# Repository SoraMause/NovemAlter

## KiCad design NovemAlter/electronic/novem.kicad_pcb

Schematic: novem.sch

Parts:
BZ1: Bz; CSS-0575A-SMT
C1: 470u; CP_Elec_8x10.5
C2, C11, C17: 10u; C_0603_HandSoldering_silk
C3: 22u; C_0603_HandSoldering_silk
C4, C10, C12, C13, C14, C16, C18, C20, C21, C23, C24: 0.1u; C_0603_HandSoldering_silk
C5, C6, C26: 10u; C_0805_HandSoldering_silk
C7, C30: 47u; C_1206_HandSoldering
C8, C28: 0.33u; C_0603_HandSoldering_silk
C9: 0.01u; C_0603_HandSoldering_silk
C15: 1u; C_0603_HandSoldering_silk
C19: 4.7u; C_0603_HandSoldering_silk
C22, C25, C27, C29: 2.2u; C_0603_HandSoldering_silk
CN1: CONNECT; Pin_Header_Straight_1x02_Pitch2.54mm
D1, D2, D4, D5: LED_ALT; IRED_D5.0mm_angled
D3, D7, D8: LED; LED_0603_HandSoldering_silk
D6: D; D_0603
D9: LATBT66B
J1: Conn_01x02_Female; Pin_Header_Straight_2x01_Pitch2.54mm
Q1: IRLML6402; SOT-23_Handsoldering
Q2, Q3, Q8, Q9: 2N7002; SOT-23_Handsoldering
Q4, Q5, Q6, Q7: Q_Photo_NPN; ST-1KL3A
R1, R6: 330; R_0603_HandSoldering_silk
R2, R3, R7, R14, R17, R23, R25, R26: 10k; R_0603_HandSoldering_silk
R4, R8: R; R_0805_HandSoldering_silk
R5, R9: 2.2k; R_0603_HandSoldering_silk
R10, R11, R12, R15, R16, R18, R19, R20, R21, R22: 1k; R_0603_HandSoldering_silk
R13: 510; R_0603_HandSoldering_silk
R24: 56k; R_0603_HandSoldering_silk
SW1: SW_SPST; PCM12SMTR
SW2, SW4: SW_Push; SKRPACE010
SW3: RESET; SKRPACE010
U1, U2: 1717_ie2_1024; Pin_Header_Straight_2x03_Pitch2.54mm
U3: AZ1117-5.0; SOT-223
U4: NJM2884-3.3; SOT-89-5_Housing_Handsoldering
U5: MPU-6500; QFN-24_3x3mm_Pitch0.4mm_silk
U6, U10: TB6614FNG; SSOP-16_4.4x5.2mm_Pitch0.65mm
U7: CSTCE12M0G52A; CSTCE12M0G52A-R0_HandSolding
U8: conn_02*03; SBH51LPSED03STBK
U9: STM32F405RGT; LQFP-64_10x10mm_Pitch0.5mm
U11: NJM2884-3.3; SOT-89-5_Housing

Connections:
+3V3: C26.1, C29.1, D4.2, D5.2, U11.4
GND: C1.2, C2.2, C3.2, C4.1, C5.2, C6.2, C7.2, C8.2, C9.2, C10.2, C11.1, C12.1, C13.2, C14.2, C15.2, C16.2, C17.1, C18.1, C19.2, C20.2, C21.2, C22.2, C23.2, C24.1, C25.1, C26.2, C27.1, C28.2, C29.2, C30.2, CN1.2, Q2.2 (S), Q3.2 (S), Q8.2 (S), Q9.2 (S), R3.2, R5.2, R7.2, R10.2, R11.2, R12.2, R14.1, R15.2, R16.2, R23.2, R24.2, R25.2, SW1.2, SW2.2, SW3.1, SW4.2, U1.3, U2.3, U3.1 (GND), U4.2, U5.11, U5.18, U5.20, U6.1, U6.5, U6.12, U7.2, U8.4, U9.12, U9.18, U9.63, U10.1, U10.5, U10.12, U11.2
IN1_L: U6.2, U9.36
IN1_R: U9.40, U10.2
IN2_L: U6.3, U9.35
IN2_R: U9.39, U10.3
MOTOR_L1: U1.1, U6.6, U6.7
MOTOR_L2: U1.2, U6.10, U6.11
MOTOR_R1: U2.1, U10.6, U10.7
MOTOR_R2: U2.2, U10.10, U10.11
unnamed: BZ1.2, D6.2, Q8.3 (D)
unnamed: C13.1, U5.10
unnamed: C14.1, SW3.2, U9.7
unnamed: C22.1, U9.31
unnamed: C25.2, U9.47
unnamed: D1.1, R8.1
unnamed: D1.2, D4.1
unnamed: D2.1, R4.1
unnamed: D2.2, D5.1
unnamed: D3.1, R5.1
unnamed: D7.1, R20.2
unnamed: D8.1, R21.2
unnamed: D9.1, R18.1
unnamed: D9.3, R22.1
unnamed: D9.4, R19.1
unnamed: J1.2, Q9.3 (D)
unnamed: Q1.1 (G), R2.1, SW1.1
unnamed: Q2.1 (G), R1.1, R3.1
unnamed: Q2.3 (D), R4.2
unnamed: Q3.1 (G), R6.1, R7.1
unnamed: Q3.3 (D), R8.2
unnamed: Q8.1 (G), R13.1, R14.2
unnamed: R24.1, U9.28
unnamed: U7.1, U9.5
unnamed: U7.3, U9.6
PWM_L: U6.14, U9.22
PWM_R: U9.23, U10.14
SCL: U5.23, U9.51
SD0: U5.9, U9.52
SDI: U5.24, U9.53
VBAT: C1.1, C2.1, C11.2, C17.2, D3.2, Q1.3 (D), R9.1, U3.3 (VI), U6.8, U6.9, U10.8, U10.9
VCC: C3.1, C5.1, C6.1, C8.1, C28.1, U1.4, U2.4, U3.2 (VO), U3.4, U4.1, U4.5, U11.1, U11.5
VDD: BZ1.1, C7.1, C9.1, C10.1, C12.2, C15.1, C16.1, C18.2, C19.1, C20.1, C21.1, C23.1, C24.2, C27.2, C30.1, D6.1, D7.2, D8.2, D9.2, Q4.1, Q5.1, Q6.1, Q7.1, R17.2, R26.2, U4.4, U5.8, U5.13, U6.15, U6.16, U8.1, U9.1, U9.13, U9.19, U9.32, U9.48, U9.64, U10.15, U10.16
batt_analog: C4.2, R9.2, R10.1, U9.25
boot: R23.1, U8.6, U9.60
buzzer_pwm: R13.2, U9.21
enc_LA: U1.5, U9.38
enc_LB: U1.6, U9.37
enc_RA: U2.5, U9.42
enc_RB: U2.6, U9.41
fledblue: R22.2, U9.3
fledgreen: R19.2, U9.62
fledred: R18.2, U9.61
fun: Q9.1 (G), R25.1, U9.55
fun_power: CN1.1, J1.1, Q1.2 (S), R2.2
gyro_cs: U5.22, U9.59
led1: R20.1, U9.20
led2: R21.1, U9.56
push1: R17.1, SW2.1, U9.24
push2: R26.1, SW4.1, U9.27
sensor0: Q4.2, R11.1, U9.8
sensor1: Q6.2, R15.1, U9.9
sensor2: Q5.2, R12.1, U9.16
sensor3: Q7.2, R16.1, U9.17
sensor_paluse_front: R1.2, U9.15
sensor_paluse_side: R6.2, U9.14
usart3_rx: U8.2, U9.30
usart3_tx: U8.3, U9.29

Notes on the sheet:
Use VCC Power
MOTOR,ENCODER
IRLED SFH4550
USE VDD LINE
BUZZER
LED,PUSHSW
WALL SENSOR ST-1KL3A
MCU
POWER
GYRO MPU-6500
MOTOR DRIVER

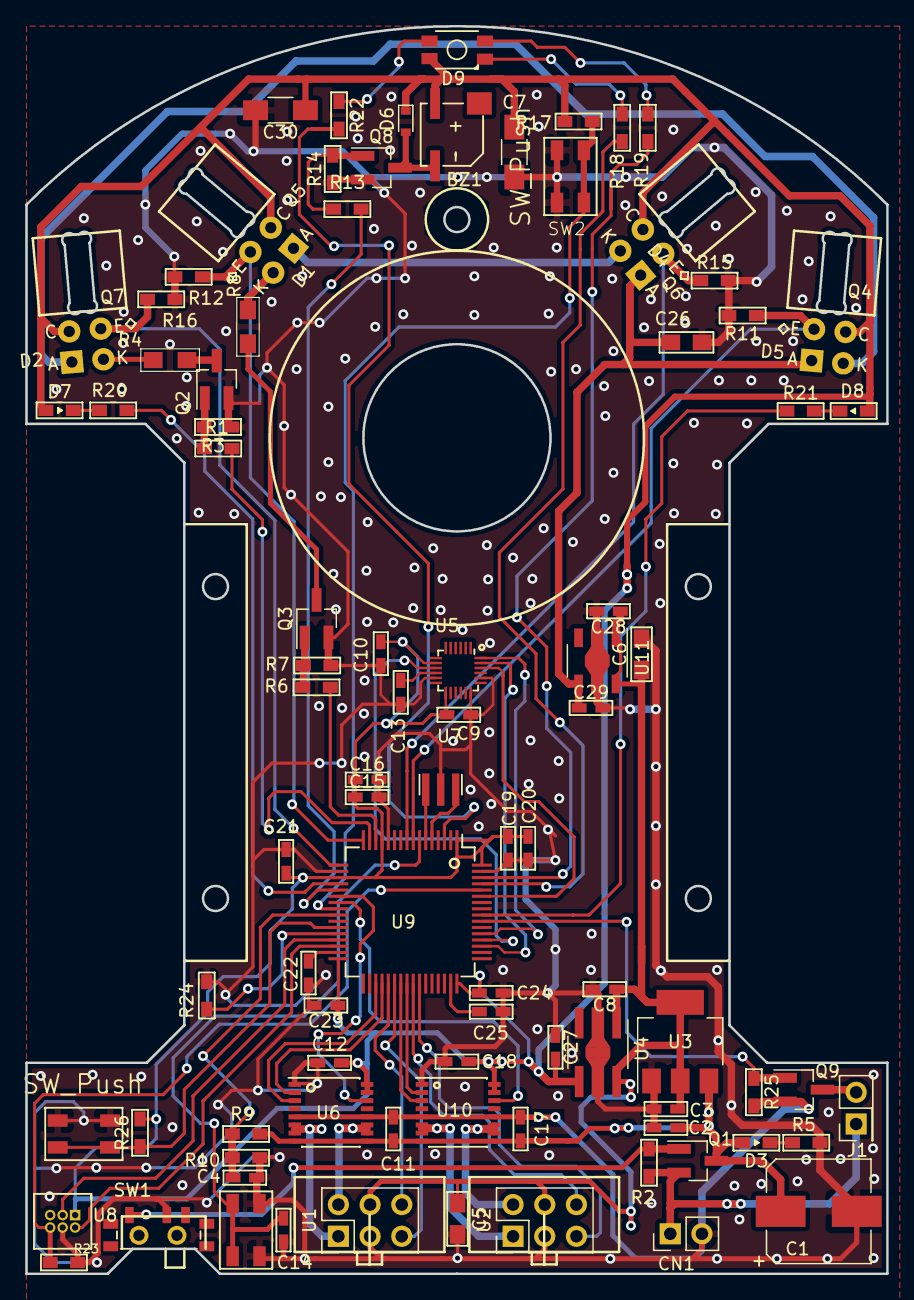
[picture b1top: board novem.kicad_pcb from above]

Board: 2 copper layers, 69.0 x 100.0 mm, 92 parts (0 on the bottom side), 68 nets.

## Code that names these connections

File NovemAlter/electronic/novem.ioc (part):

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Mcu.Name=STM32F405RGTx
Mcu.Package=LQFP64
Mcu.UserName=STM32F405RGTx
PA0-WKUP.GPIOParameters=GPIO_Label
PA0-WKUP.GPIO_Label=sensor_paluseSide
PA0-WKUP.Signal=GPIO_Output
PA1.GPIOParameters=GPIO_Label
PA1.GPIO_Label=sensor_paluseFront
PA1.Signal=GPIO_Output
PA2.Signal=ADCx_IN2
PA3.Signal=ADCx_IN3
PA4.GPIOParameters=GPIO_Label
PA4.GPIO_Label=led1
PA4.Signal=GPIO_Output
PA5.Signal=S_TIM2_CH1_ETR
PA6.Signal=S_TIM3_CH1
PA7.Signal=S_TIM3_CH2
PA8.Signal=S_TIM1_CH1
PA9.Signal=S_TIM1_CH2
PB1.GPIOParameters=GPIO_Label
PB1.GPIO_Label=push_sw2
PB1.Signal=GPIO_Input
PB10.Mode=Asynchronous
PB10.Signal=USART3_TX
PB11.Mode=Asynchronous
PB11.Signal=USART3_RX
PB14.GPIOParameters=GPIO_Label
PB14.GPIO_Label=IN2_L
PB14.Signal=GPIO_Output
PB15.GPIOParameters=GPIO_Label
PB15.GPIO_Label=IN1_L
PB15.Signal=GPIO_Output
PB3.Signal=S_TIM2_CH2
PB4.GPIOParameters=GPIO_Label
PB4.GPIO_Label=led2
PB4.Signal=GPIO_Output
PB7.GPIOParameters=GPIO_Label
PB7.GPIO_Label=gyro_cs
PB7.Signal=GPIO_Output
PB8.GPIOParameters=GPIO_Label
PB8.GPIO_Label=fledred
PB8.Signal=GPIO_Output
PB9.GPIOParameters=GPIO_Label
PB9.GPIO_Label=fledgreen
PB9.Signal=GPIO_Output
PC0.Signal=ADCx_IN10
PC1.Signal=ADCx_IN11
PC10.Mode=Full_Duplex_Master
PC10.Signal=SPI3_SCK
PC11.Mode=Full_Duplex_Master
PC11.Signal=SPI3_MISO
PC12.Mode=Full_Duplex_Master
PC12.Signal=SPI3_MOSI
PC14-OSC32_IN.GPIOParameters=GPIO_Label
PC14-OSC32_IN.GPIO_Label=fled_blue
PC14-OSC32_IN.Signal=GPIO_Output
PC4.GPIOParameters=GPIO_Label
PC4.GPIO_Label=pushsw1
PC4.Signal=GPIO_Input
PC5.Signal=ADCx_IN15
PC6.Signal=S_TIM8_CH1
PC7.Signal=S_TIM8_CH2
PC8.GPIOParameters=GPIO_Label
PC8.GPIO_Label=IN2_R
PC8.Signal=GPIO_Output
PC9.GPIOParameters=GPIO_Label
PC9.GPIO_Label=IN1_R
PC9.Signal=GPIO_Output
PH0-OSC_IN.Mode=HSE-External-Oscillator
PH0-OSC_IN.Signal=RCC_OSC_IN
PH1-OSC_OUT.Mode=HSE-External-Oscillator
PH1-OSC_OUT.Signal=RCC_OSC_OUT
RCC.HSE_VALUE=20000000
RCC.SYSCLKFreq_VALUE=160000000
RCC.SYSCLKSource=RCC_SYSCLKSOURCE_PLLCLK
board=novem

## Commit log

2019-02-16 initial program
2019-02-24 ひとまず走る
2019-02-25 ターン速度1600mm/s
2019-03-24 電通大プチコン
2019-04-29 minor change
2019-04-29 add max parameter
2019-07-13 マウス合宿 訂正var
2019-07-13 fun duty change
